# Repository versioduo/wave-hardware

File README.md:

# wave-hardware
🔊 MA12070P Class-D Amplifier

## Board

## Schematic

[PDF](wave.pdf)

## Bill Of Materials

[Interactive BOM](https://htmlpreview.github.io/?https://github.com/versioduo/wave-hardware/main/wave-bom.html)

# Copying
Anyone can use this public domain work without having to seek authorisation, no one can ever own it.

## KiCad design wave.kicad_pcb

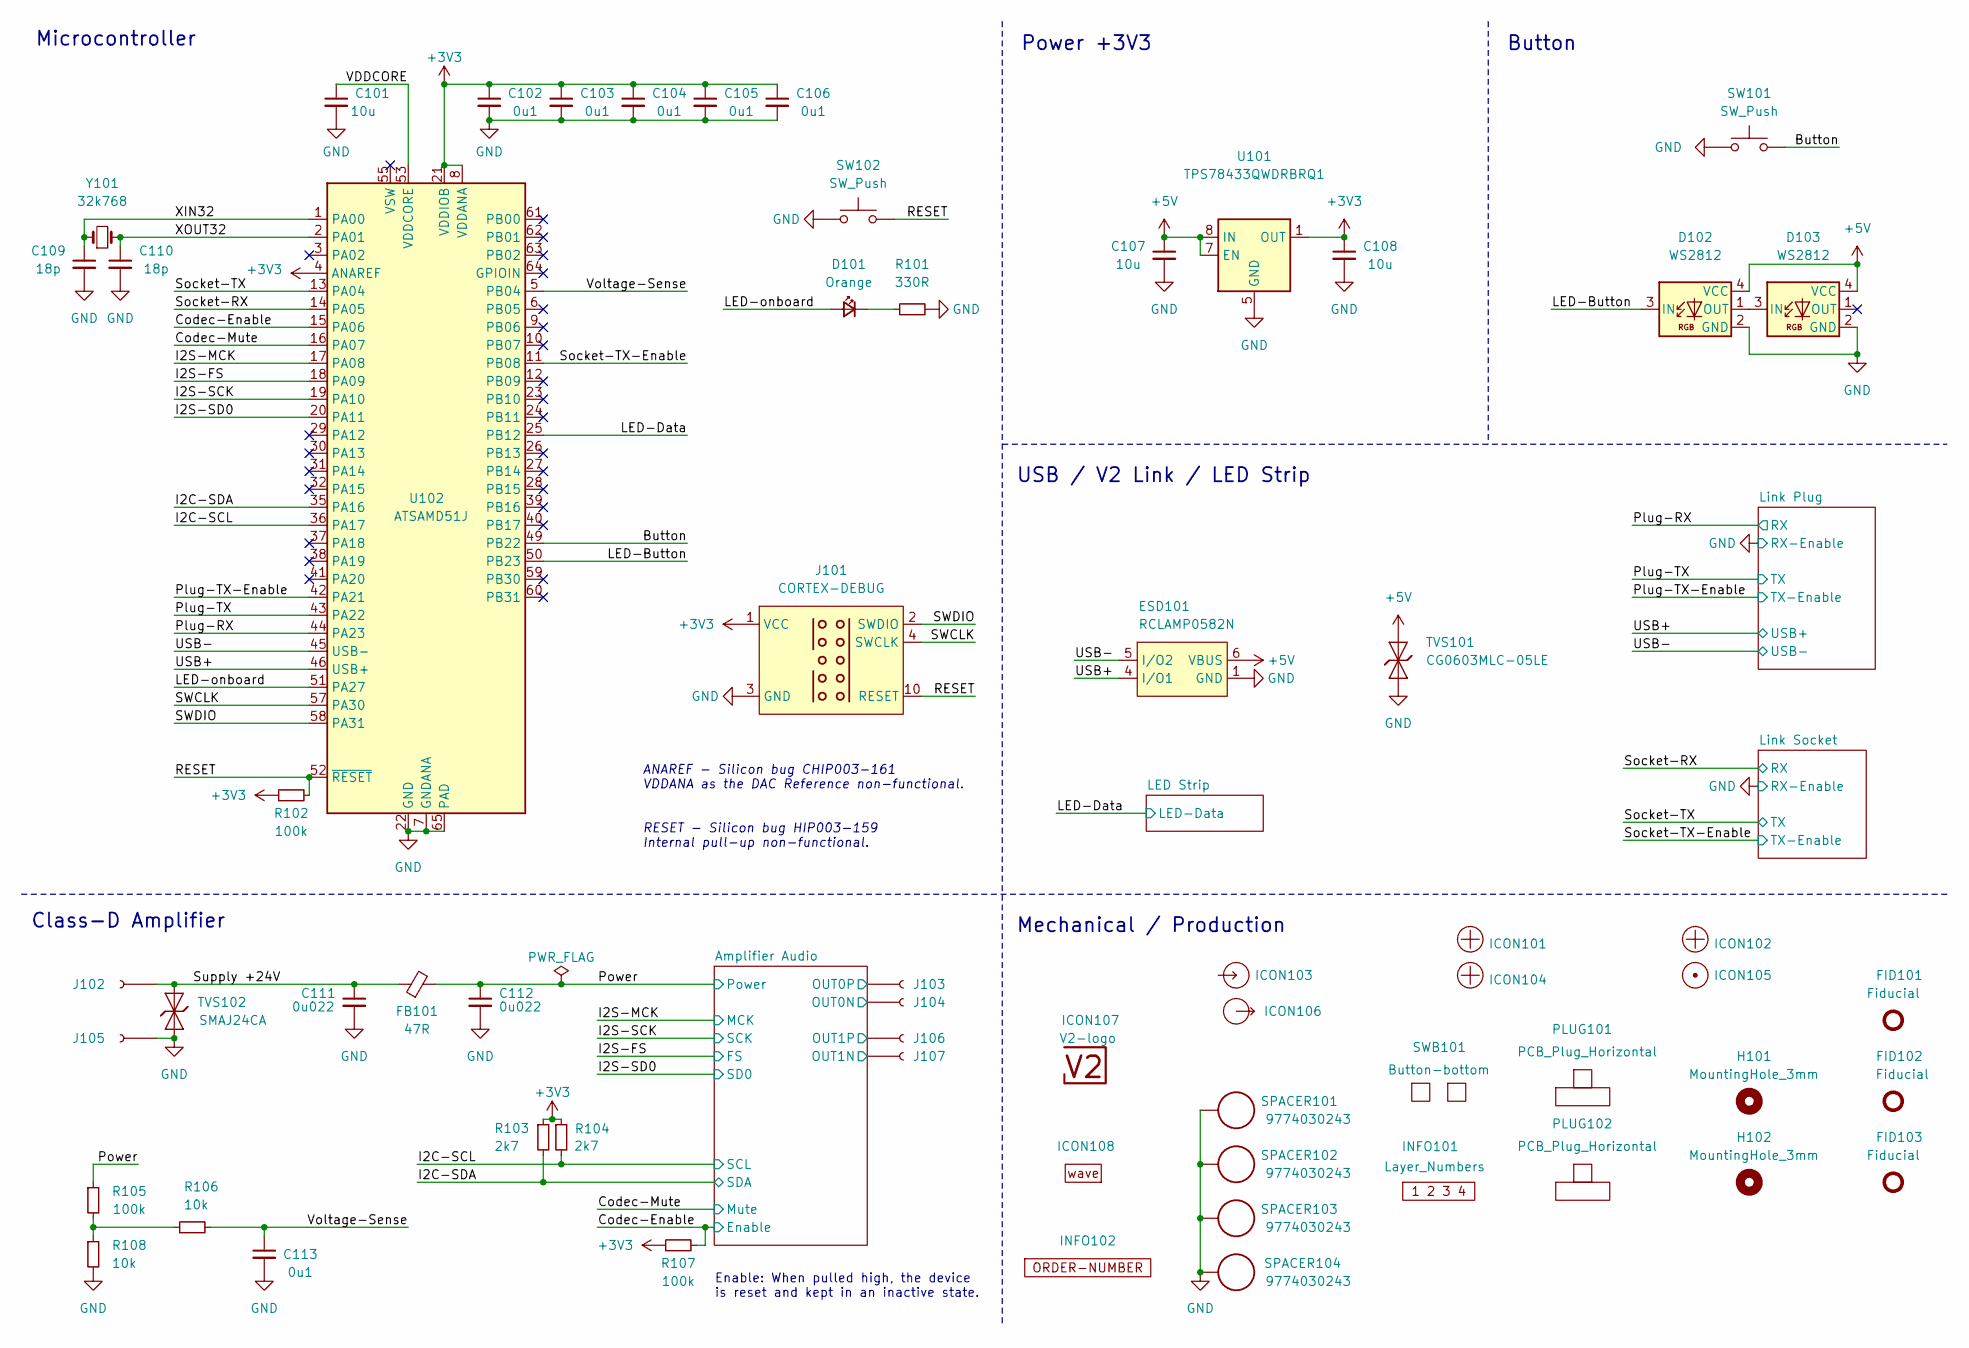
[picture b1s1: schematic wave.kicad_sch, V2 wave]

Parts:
C101, C107, C108: 10u; C_0603_1608Metric
C102, C103, C104, C105, C106, C113: 0u1; C_0603_1608Metric
C109, C110: 18p; C_0603_1608Metric
C111, C112: 0u022; C_0603_1608Metric
D101: Orange; LED_0603_1608Metric
D102, D103: WS2812; WS2812-2020
ESD101: RCLAMP0582N; SLP1210N6
FB101: 47R; L_3.1x5.1
FID101, FID102, FID103: Fiducial; Fiducial_0.5mm_Mask1mm_Paste
H101, H102: MountingHole_3mm
ICON101, ICON102, ICON104: Plus; Plus_Small
ICON103: Arrow_In
ICON105: Dot; Dot_Small
ICON106: Arrow_Out
ICON107: V2-logo; Logo_Small
ICON108: Board_wave; Board_wave_Small
INFO101: Layer_Numbers
INFO102: ORDER-NUMBER; Order_Number
J101: CORTEX-DEBUG; Cortex_Debug_Pad
J102, J103, J104, J105, J106, J107: WAGO-2065; 2065-100
PLUG101, PLUG102: PCB_Plug_Horizontal
R101: 330R; R_0603_1608Metric
R102, R105, R107: 100k; R_0603_1608Metric
R103, R104: 2k7; R_0603_1608Metric
R106, R108: 10k; R_0603_1608Metric
SPACER101, SPACER102, SPACER103, SPACER104: 9774030243
SW101, SW102: SW_Push; SKSG
SWB101: Button-bottom; PCB_Button-bottom
TVS101: CG0603MLC-05LE; D_0603_1608Metric
TVS102: SMAJ24CA; D_SMA
U101: TPS78433QWDRBRQ1; VSON-8-1_3x3mm_P0.65_EP1.65x2.4mm
U102: ATSAMD51J; QFN-64-1EP_9x9mm_P0.5mm_EP4.8x4.8mm_ThermalVias
Y101: 32k768; Crystal_SMD_3215-2Pin_3.2x1.5mm

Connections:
+3V3: C102.1, C103.1, C104.1, C105.1, C106.1, C108.1, J101.1 (VCC), R102.1, R103.1, R104.1, R107.1, U101.1 (OUT), U102.4 (ANAREF), U102.8 (VDDANA), U102.21 (VDDIOB), U102.34 (VDDIO), U102.48 (VDDIO), U102.56 (VDDIO); also elsewhere on the board
+5V: C107.1, D102.4 (VCC), D103.4 (VCC), ESD101.6 (VBUS), TVS101.2 (A), U101.7 (EN), U101.8 (IN); also elsewhere on the board
/Amplifier Audio/OUT0N: J104.1; also elsewhere on the board
/Amplifier Audio/OUT0P: J103.1; also elsewhere on the board
/Amplifier Audio/OUT1N: J107.1; also elsewhere on the board
/Amplifier Audio/OUT1P: J106.1; also elsewhere on the board
/Button: SW101.2, U102.49 (PB22)
/Codec-Enable: R107.2, U102.15 (PA06); also elsewhere on the board
/Codec-Mute: U102.16 (PA07); also elsewhere on the board
/I2C-SCL: R104.2, U102.36 (PA17); also elsewhere on the board
/I2C-SDA: R103.2, U102.35 (PA16); also elsewhere on the board
/I2S-FS: U102.18 (PA09); also elsewhere on the board
/I2S-MCK: U102.17 (PA08); also elsewhere on the board
/I2S-SCK: U102.19 (PA10); also elsewhere on the board
/I2S-SD0: U102.20 (PA11); also elsewhere on the board
/LED-Button: D102.3 (IN), U102.50 (PB23)
/LED-Data: U102.25 (PB12); also elsewhere on the board
/LED-onboard: D101.2 (A), U102.51 (PA27)
/Plug-RX: U102.44 (PA23); also elsewhere on the board
/Plug-TX: U102.43 (PA22); also elsewhere on the board
/Plug-TX-Enable: U102.42 (PA21); also elsewhere on the board
/Power: C112.1, FB101.2, R105.1; also elsewhere on the board
/RESET: J101.10 (RESET), R102.2, SW102.2, U102.52 (~RESET)
/SWCLK: J101.4 (SWCLK), U102.57 (PA30)
/SWDIO: J101.2 (SWDIO), U102.58 (PA31)
/Socket-RX: U102.14 (PA05); also elsewhere on the board
/Socket-TX: U102.13 (PA04); also elsewhere on the board
/Socket-TX-Enable: U102.11 (PB08); also elsewhere on the board
/Supply +24V: C111.1, FB101.1, J102.1, TVS102.2 (A)
/USB+: ESD101.4 (I/O1), U102.46 (USB+); also elsewhere on the board
/USB-: ESD101.5 (I/O2), U102.45 (USB-); also elsewhere on the board
/VDDCORE: C101.1, U102.53 (VDDCORE)
/Voltage-Sense: C113.1, R106.2, U102.5 (PB04)
/XIN32: C109.1, U102.1 (PA00), Y101.1
/XOUT32: C110.1, U102.2 (PA01), Y101.2
GND: C101.2, C102.2, C103.2, C104.2, C105.2, C106.2, C107.2, C108.2, C109.2, C110.2, C111.2, C112.2, C113.2, D102.2 (GND), D103.2 (GND), ESD101.1 (GND), J101.3 (GND), J101.5 (GND), J105.1, R101.2, R108.2, SPACER101.1, SPACER102.1, SPACER103.1, SPACER104.1, SW101.1, SW102.1, TVS101.1 (K), TVS102.1 (K), U101.5 (GND), U101.9 (GND), U102.7 (GNDANA), U102.22 (GND), U102.33 (GND), U102.47 (GND), U102.54 (GND), U102.65 (PAD); also elsewhere on the board
unnamed: D101.1 (K), R101.1
unnamed: D102.1 (OUT), D103.3 (IN)
unnamed: R105.2, R106.1, R108.1

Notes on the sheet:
﻿ANAREF - Silicon bug CHIP003-161 VDDANA as the DAC Reference non-functional.
RESET - ﻿Silicon bug HIP003-159 Internal pull-up non-functional.
Button
USB / V2 Link / LED Strip
Mechanical / Production
Power +3V3
Enable: When pulled high, the device is reset and kept in an inactive state.
Microcontroller
Class-D Amplifier

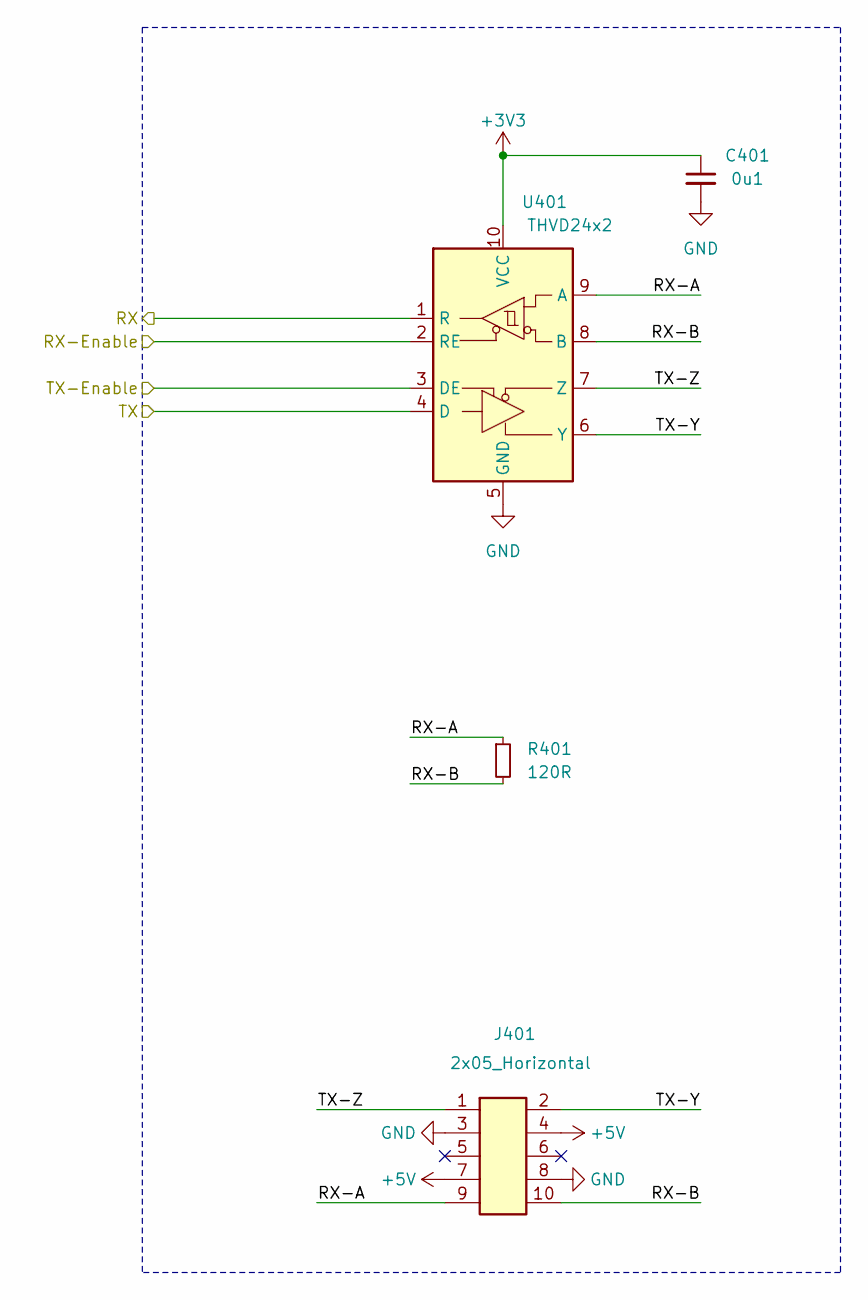
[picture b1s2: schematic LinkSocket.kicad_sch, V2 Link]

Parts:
C401: 0u1; C_0603_1608Metric
J401: 2x05_Horizontal; PinHeader_2x05_P1.27mm_Horizontal
R401: 120R; R_0603_1608Metric
U401: THVD24x2; VSON-10-4-1EP_3x3mm_P0.5mm_EP1.65x2.4mm_ThermalVias

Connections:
+3V3: C401.1, U401.10 (VCC); also elsewhere on the board
+5V: J401.4, J401.7; also elsewhere on the board
/Link Socket/RX-A: J401.9, R401.1, U401.9 (A)
/Link Socket/RX-B: J401.10, R401.2, U401.8 (B)
/Link Socket/TX-Y: J401.2, U401.6 (Y)
/Link Socket/TX-Z: J401.1, U401.7 (Z)
/Socket-RX: U401.1 (R); also elsewhere on the board
/Socket-TX: U401.4 (D); also elsewhere on the board
/Socket-TX-Enable: U401.3 (DE); also elsewhere on the board
GND: C401.2, J401.3, J401.8, U401.2 (RE), U401.5 (GND), U401.11 (GND); also elsewhere on the board

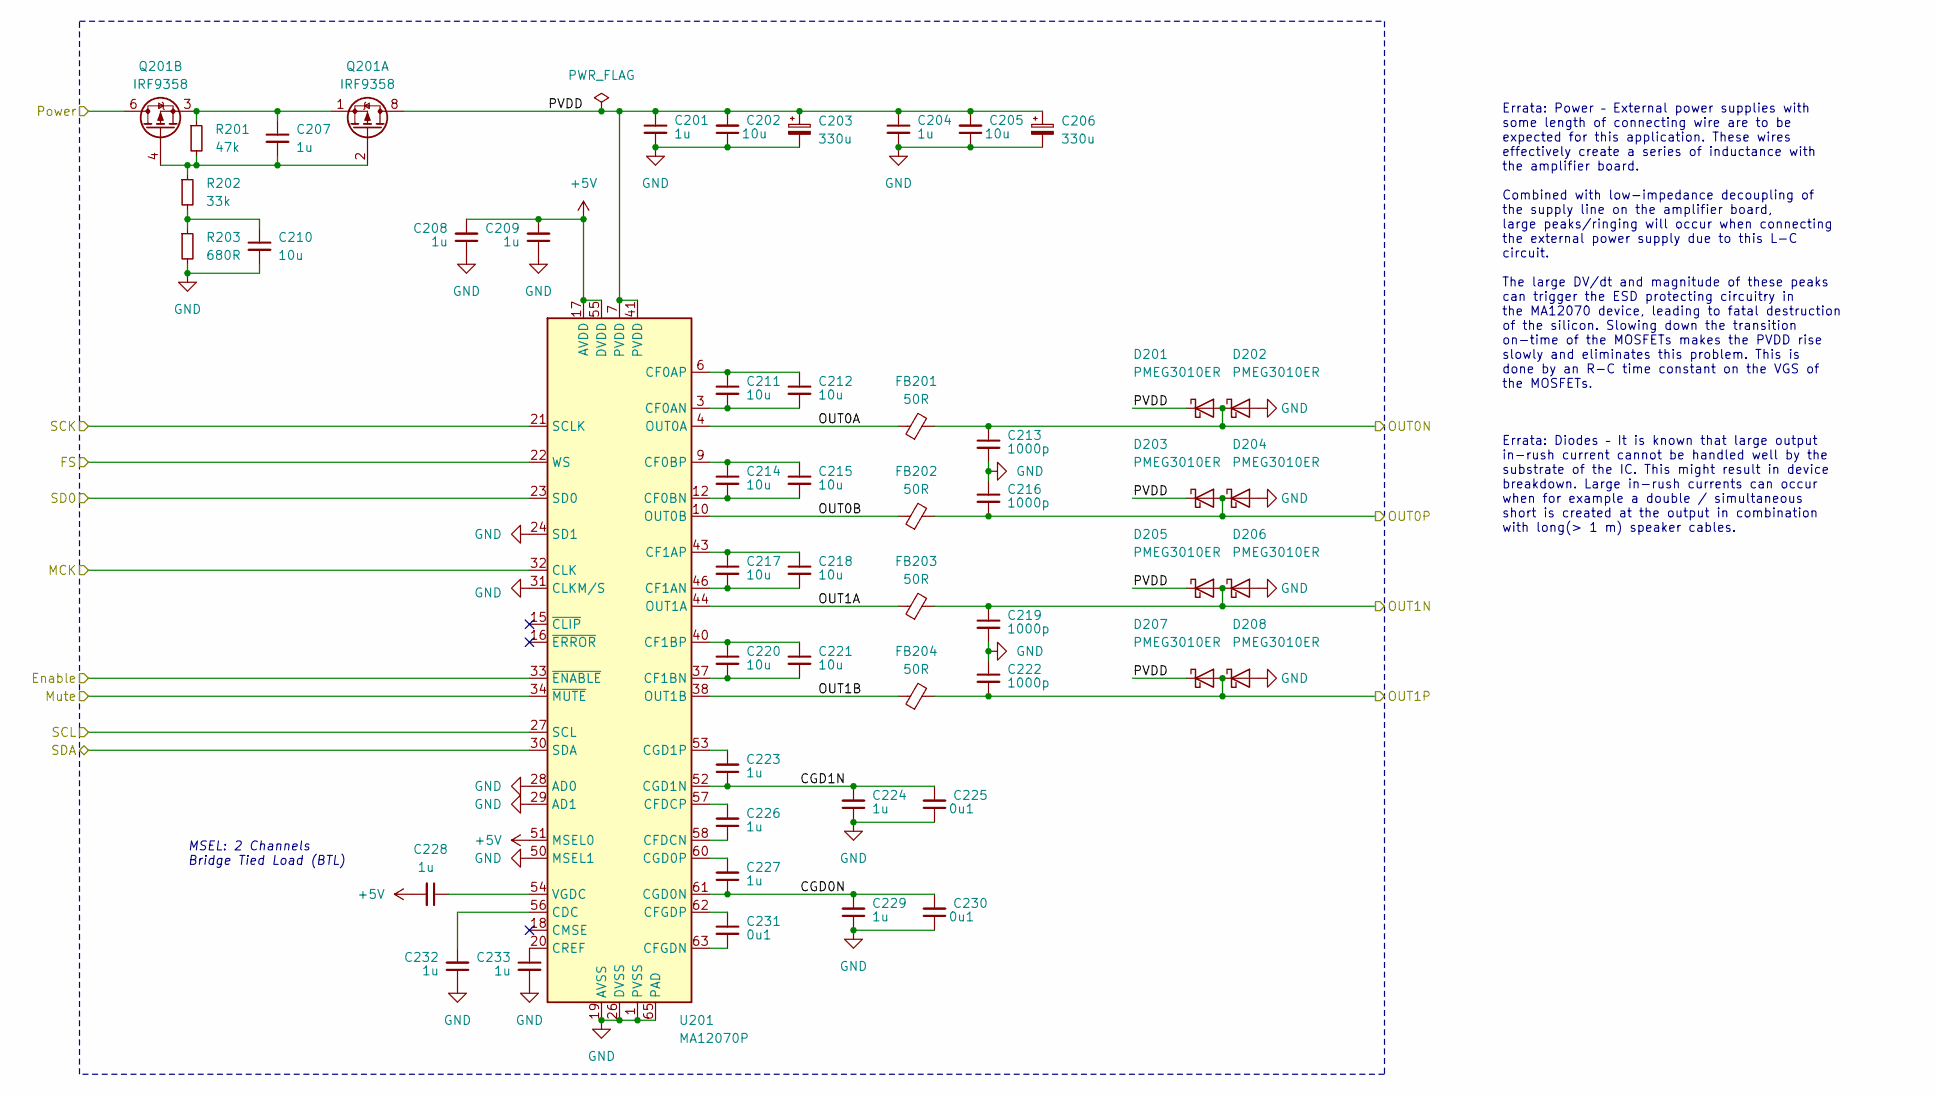
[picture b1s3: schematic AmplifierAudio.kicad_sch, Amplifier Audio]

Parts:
C201, C204, C207, C208, C209, C223, C224, C226, C227, C228, C229, C232, C233: 1u; C_0603_1608Metric
C202, C205, C210, C211, C212, C214, C215, C217, C218, C220, C221: 10u; C_0805_2012Metric
C203, C206: 330u; CP_Elec_8x10
C213, C216, C219, C222: 1000p; C_0603_1608Metric
C225, C230, C231: 0u1; C_0603_1608Metric
D201, D202, D203, D204, D205, D206, D207, D208: PMEG3010ER; Nexperia_CFP3_SOD-123W
FB201, FB202, FB203, FB204: 50R; L_1206_3216Metric
Q201: IRF9358; SOIC-8_3.9x4.9mm_P1.27mm
R201: 47k; R_0603_1608Metric
R202: 33k; R_0603_1608Metric
R203: 680R; R_0603_1608Metric
U201: MA12070P; QFN-64-1EP_9x9mm_P0.5mm_EP5.45x5.45mm_ThermalVias

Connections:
+5V: C208.2, C209.2, C228.2, U201.17 (AVDD), U201.51 (MSEL0), U201.55 (DVDD); also elsewhere on the board
/Amplifier Audio/CGD0N: C227.1, C229.2, C230.2, U201.61 (CGD0N)
/Amplifier Audio/CGD1N: C223.1, C224.2, C225.2, U201.52 (CGD1N)
/Amplifier Audio/OUT0A: FB201.1, U201.4 (OUT0A), U201.5 (OUT0A)
/Amplifier Audio/OUT0B: FB202.1, U201.10 (OUT0B), U201.11 (OUT0B)
/Amplifier Audio/OUT0N: C213.1, D201.2 (A), D202.1 (K), FB201.2; also elsewhere on the board
/Amplifier Audio/OUT0P: C216.2, D203.2 (A), D204.1 (K), FB202.2; also elsewhere on the board
/Amplifier Audio/OUT1A: FB203.1, U201.44 (OUT1A), U201.45 (OUT1A)
/Amplifier Audio/OUT1B: FB204.1, U201.38 (OUT1B), U201.39 (OUT1B)
/Amplifier Audio/OUT1N: C219.1, D205.2 (A), D206.1 (K), FB203.2; also elsewhere on the board
/Amplifier Audio/OUT1P: C222.2, D207.2 (A), D208.1 (K), FB204.2; also elsewhere on the board
/Amplifier Audio/PVDD: C201.1, C202.2, C203.1, C204.1, C205.2, C206.1, D201.1 (K), D203.1 (K), D205.1 (K), D207.1 (K), Q201.7 (D1), Q201.8 (D1), U201.7 (PVDD), U201.8 (PVDD), U201.41 (PVDD), U201.42 (PVDD)
/Codec-Enable: U201.33 (~ENABLE); also elsewhere on the board
/Codec-Mute: U201.34 (~MUTE); also elsewhere on the board
/I2C-SCL: U201.27 (SCL); also elsewhere on the board
/I2C-SDA: U201.30 (SDA); also elsewhere on the board
/I2S-FS: U201.22 (WS); also elsewhere on the board
/I2S-MCK: U201.32 (CLK); also elsewhere on the board
/I2S-SCK: U201.21 (SCLK); also elsewhere on the board
/I2S-SD0: U201.23 (SD0); also elsewhere on the board
/Power: Q201.5 (D2), Q201.6 (D2); also elsewhere on the board
GND: C201.2, C202.1, C203.2, C204.2, C205.1, C206.2, C208.1, C209.1, C210.2, C213.2, C216.1, C219.2, C222.1, C224.1, C225.1, C229.1, C230.1, C232.1, C233.2, D202.2 (A), D204.2 (A), D206.2 (A), D208.2 (A), R203.2, U201.1 (PVSS), U201.2 (PVSS), U201.13 (PVSS), U201.14 (PVSS), U201.19 (AVSS), U201.24 (SD1), U201.25 (AVSS), U201.26 (DVSS), U201.28 (AD0), U201.29 (AD1), U201.31 (CLKM/S), U201.35 (PVSS), U201.36 (PVSS), U201.47 (PVSS), U201.48 (PVSS), U201.50 (MSEL1), U201.59 (DVSS), U201.65 (PAD); also elsewhere on the board
unnamed: C210.1, R202.2, R203.1
unnamed: C207.2, Q201.2 (G1), Q201.4 (G2), R201.2, R202.1
unnamed: C207.1, Q201.1 (S1), Q201.3 (S2), R201.1
unnamed: C232.2, U201.56 (CDC)
unnamed: C211.2, C212.2, U201.3 (CF0AN)
unnamed: C211.1, C212.1, U201.6 (CF0AP)
unnamed: C214.2, C215.2, U201.12 (CF0BN)
unnamed: C214.1, C215.1, U201.9 (CF0BP)
unnamed: C217.2, C218.2, U201.46 (CF1AN)
unnamed: C217.1, C218.1, U201.43 (CF1AP)
unnamed: C220.2, C221.2, U201.37 (CF1BN)
unnamed: C220.1, C221.1, U201.40 (CF1BP)
unnamed: C226.1, U201.58 (CFDCN)
unnamed: C226.2, U201.57 (CFDCP)
unnamed: C231.2, U201.63 (CFGDN)
unnamed: C231.1, U201.62 (CFGDP)
unnamed: C227.2, U201.60 (CGD0P)
unnamed: C223.2, U201.53 (CGD1P)
unnamed: C233.1, U201.20 (CREF)
unnamed: C228.1, U201.54 (VGDC)

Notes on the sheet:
Errata: Diodes – It is known that large output in-rush current cannot be handled well by the substrate of the IC. This might result in device breakdown. Large in-rush currents can occur when for example a double / simultaneous short is created at the output in combination with long(> 1 m) speaker c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
MSEL: 2 Channels Bridge Tied Load (BTL)
Errata: Power – External power supplies with some length of connecting wire are to be expected for this application. These wires effectively create a series of inductance with the amplifier board. Combined with low-impedance decoupling of the supply line on the amplifier board, large peaks/ringing 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

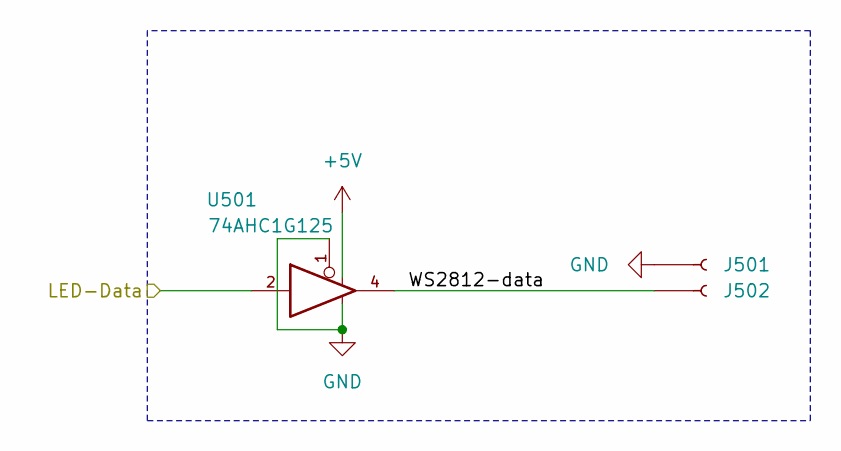
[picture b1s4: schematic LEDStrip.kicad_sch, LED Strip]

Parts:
J501, J502: WAGO-2065; 2065-100
U501: 74AHC1G125; SOT-23-5

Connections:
+5V: U501.5; also elsewhere on the board
/LED Strip/WS2812-data: J502.1, U501.4
/LED-Data: U501.2; also elsewhere on the board
GND: J501.1, U501.1, U501.3; also elsewhere on the board

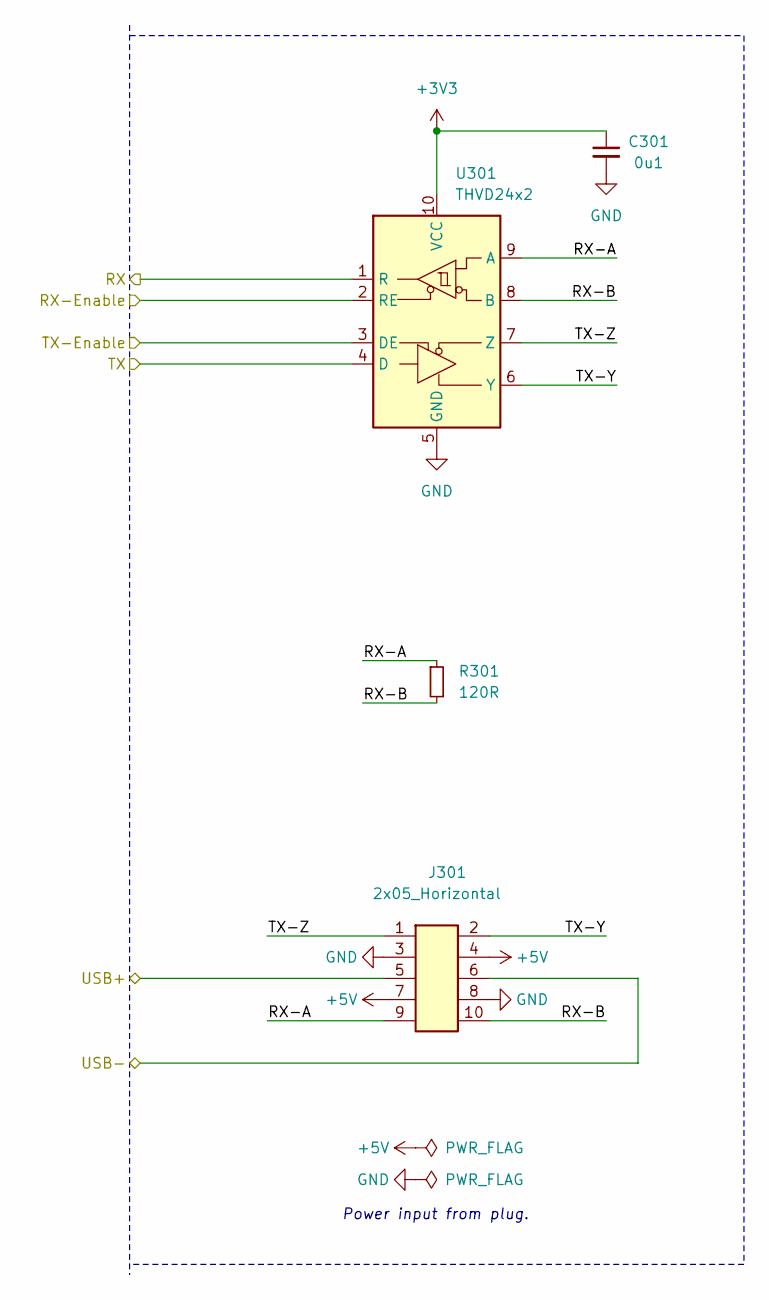
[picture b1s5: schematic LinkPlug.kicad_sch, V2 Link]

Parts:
C301: 0u1; C_0603_1608Metric
J301: 2x05_Horizontal; PinHeader_2x05_P1.27mm_Horizontal
R301: 120R; R_0603_1608Metric
U301: THVD24x2; VSON-10-4-1EP_3x3mm_P0.5mm_EP1.65x2.4mm_ThermalVias

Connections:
+3V3: C301.1, U301.10 (VCC); also elsewhere on the board
+5V: J301.4, J301.7; also elsewhere on the board
/Link Plug/RX-A: J301.9, R301.1, U301.9 (A)
/Link Plug/RX-B: J301.10, R301.2, U301.8 (B)
/Link Plug/TX-Y: J301.2, U301.6 (Y)
/Link Plug/TX-Z: J301.1, U301.7 (Z)
/Plug-RX: U301.1 (R); also elsewhere on the board
/Plug-TX: U301.4 (D); also elsewhere on the board
/Plug-TX-Enable: U301.3 (DE); also elsewhere on the board
/USB+: J301.5; also elsewhere on the board
/USB-: J301.6; also elsewhere on the board
GND: C301.2, J301.3, J301.8, U301.2 (RE), U301.5 (GND), U301.11 (GND); also elsewhere on the board

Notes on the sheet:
Power input from plug.

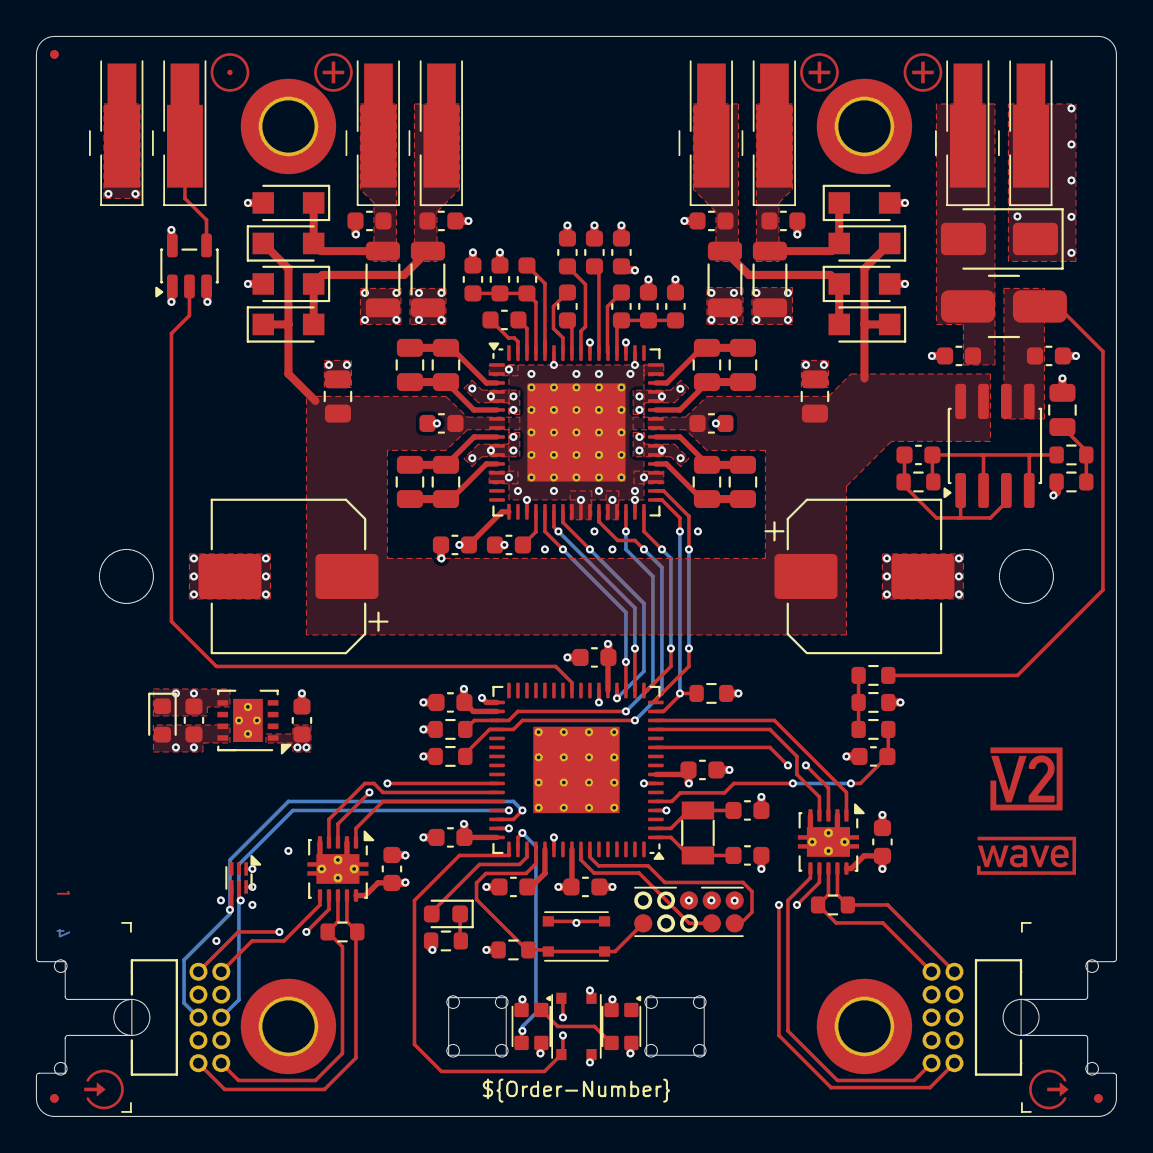
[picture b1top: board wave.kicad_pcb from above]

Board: 4 copper layers, 60.0 x 60.0 mm, 123 parts (0 on the bottom side), 75 nets.

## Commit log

2023-06-15 Import
2023-08-28 Refresh
2024-03-28 Update to Kicad 8
2024-06-20 Replace icons
